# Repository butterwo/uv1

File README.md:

# uv1
KiCad design for UV dosimeter

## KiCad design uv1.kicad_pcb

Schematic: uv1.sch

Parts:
C1: 0.22u; C_Rect_L7.0mm_W2.5mm_P5.00mm
C2: 0.47u; C_0603_1608Metric
C3: 0.01u; C_0603_1608Metric
C4, C8: 0.1u; C_0603_1608Metric
C5: 100p; C_0603_1608Metric
D1: LM285D-1.2; SOIC-8_3.9x4.9mm_P1.27mm
J1: Conn_02x07_Odd_Even; PinSocket_2x07_P2.54mm_Horizontal
J2: - +; TestPoint_2Pads_Pitch2.54mm_Drill0.8mm
R1: 47k; R_0603_1608Metric
R2: 1M; R_0603_1608Metric
R3: 100k; R_0603_1608Metric
R4: 6.8k; R_0603_1608Metric
RV1: 20k; Potentiometer_Bourns_3299W_Vertical
SW1: SW_Push; MEC_3FTH9
U1: TC7106; TQFP-44_10x10mm_P0.8mm
U2: DE115-RS-20
U3: 74AHC1G04; SOIC-14_3.9x8.7mm_P1.27mm

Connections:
+BATT: J1.1, J1.2, J1.3, J1.4, J2.1, SW1.2, U3.5 (VCC)
-BATT: C8.2, J2.2, U1.26
/ACOM: C3.2, D1.4, J1.13, J1.14, RV1.3, U1.30, U1.32, U1.35
/LCD_1A: U1.23, U2.25
/LCD_1B: U1.16, U2.24
/LCD_1BC: U1.19, U2.3
/LCD_1C: U1.24, U2.7
/LCD_1D: U1.15, U2.6
/LCD_1E: U1.18, U2.5
/LCD_1F: U1.17, U2.26
/LCD_1G: U1.22, U2.27
/LCD_2A: U1.12, U2.21
/LCD_2B: U1.11, U2.20
/LCD_2C: U1.10, U2.11
/LCD_2D: U1.9, U2.10
/LCD_2E: U1.14, U2.9
/LCD_2F: U1.13, U2.22
/LCD_2G: U1.25, U2.23
/LCD_3A: U1.5, U2.17
/LCD_3B: U1.4, U2.16
/LCD_3C: U1.3, U2.15
/LCD_3D: U1.2, U2.14
/LCD_3E: U1.8, U2.13
/LCD_3F: U1.6, U2.18
/LCD_3G: U1.7, U2.19
/LCD_-: U1.20, U2.2
/LCD_BP: U1.21, U2.1, U2.4, U2.8, U2.30, U2.31, U2.32, U3.2
/LCD_DP3: U2.12, U3.4
GND: U1.37, U3.3 (GND)
unnamed: C1.1, C2.2, R1.2
unnamed: C1.2, U1.27
unnamed: C2.1, U1.29
unnamed: C3.1, R2.1, U1.31
unnamed: C4.1, U1.33
unnamed: C4.2, U1.34
unnamed: C5.1, R3.1, U1.40
unnamed: C5.2, U1.38
unnamed: C8.1, R4.1, SW1.1, U1.1
unnamed: D1.8, R4.2, RV1.1
unnamed: J1.11, J1.12, R2.2
unnamed: R1.1, U1.28
unnamed: R3.2, U1.39
unnamed: RV1.2, U1.36

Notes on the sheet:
VREF+ should be 420 +/- 150 mV to give FS of 199mMED/hr +/- 30% **TODO Change V reference to LM185
TC7106 digits are numbered right to left DE115 digits are numbered left to right
C1 polypropylene or polyester C2, C4 mylar C3, C5 ceramic
UV radiometer
0.1
12/10/2018
Main board

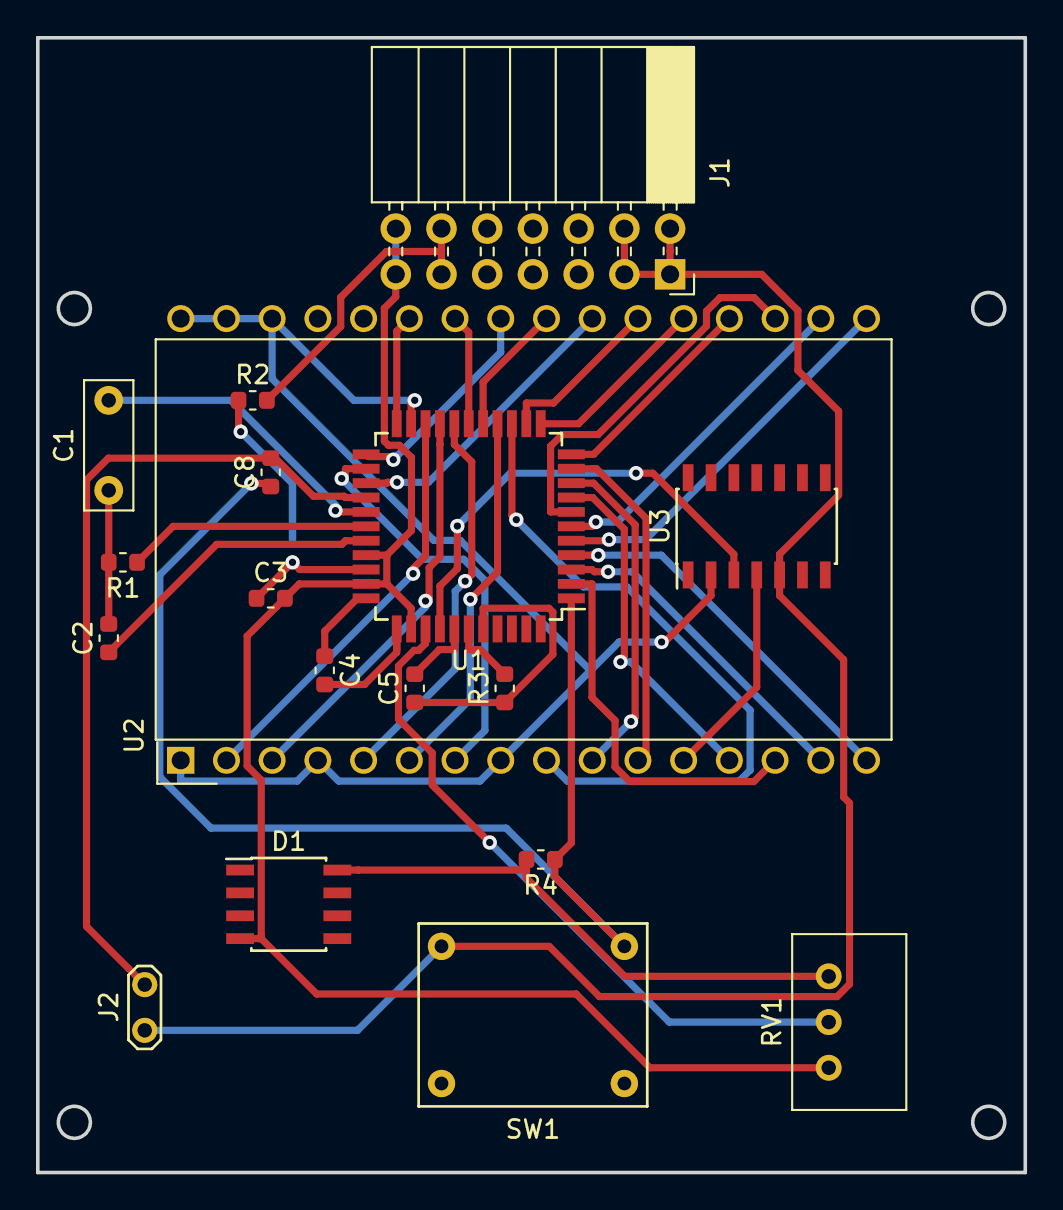
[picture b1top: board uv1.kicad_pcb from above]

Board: 2 copper layers, 54.9 x 63.0 mm, 18 parts (0 on the bottom side), 43 nets.

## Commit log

2018-10-03 Created from KiCad.gitignore template
2018-10-03 Deleted ignored files
2018-10-09 Display DE151 Sensor connector 2x 2x2 male
2018-10-10 DE115 LCD with new footprint + 3D
2018-10-10 Added 3D shapes and FreeCad dirs
2018-10-10 Correct version of DE115 FreeCAD
2018-10-10 2x7 sensor connector
2018-10-11 Updated 3d model of LCD again
2018-10-15 Fully routed by autorouter + tweaks
2018-10-16 Decoupling caps added
2018-10-16 Specified footprints for decoupling caps
2018-10-22 Commit before rerouting
2018-11-11 Before changing gate packages
2018-12-05 Haven't committed in a while....
2019-01-10 Removed last digit enable logic from uv1.sch
2019-01-10 Routed
